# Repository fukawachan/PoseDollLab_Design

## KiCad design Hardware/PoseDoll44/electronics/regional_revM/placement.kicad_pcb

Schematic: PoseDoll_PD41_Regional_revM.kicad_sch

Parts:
C1: 10u X5R 25V / CL21A106KAYNNNE; C_0805_2012Metric
C2, C4: 22u X5R 16V / CL21A226MOYNNNE; C_0805_2012Metric
C3, C5, C7, C8, C21, C22, C23, C24, C25, C26, C27, C28, C29: 100n X7R; C_0603_1608Metric
C6: 1u X7R; C_0603_1608Metric
D1: PESD5V0S2BT,215; SOT-23
D2: TPD2E2U06DCKR; SOT-323_SC-70
J1: 5V from fused pelvis star; JST_PH_B2B-PH-SM4-TB_1x02-1MP_P2.00mm_Vertical
J2: CAN IN / GND-L-H; JST_GH_BM03B-GHS-TBT_1x03-1MP_P1.25mm_Vertical
J3: CAN OUT / GND-L-H; JST_GH_BM03B-GHS-TBT_1x03-1MP_P1.25mm_Vertical
J4: USB data only; external 5V required; USB_C_Data_Port
J11: P1 sensor / CS GPIO2; JST_SH_BM06B-SRSS-TB_1x06-1MP_P1.00mm_Vertical
J12: P2 sensor / CS GPIO4; JST_SH_BM06B-SRSS-TB_1x06-1MP_P1.00mm_Vertical
J13: P3 sensor / CS GPIO5; JST_SH_BM06B-SRSS-TB_1x06-1MP_P1.00mm_Vertical
J14: P4 sensor / CS GPIO6; JST_SH_BM06B-SRSS-TB_1x06-1MP_P1.00mm_Vertical
J15: P5 sensor / CS GPIO7; JST_SH_BM06B-SRSS-TB_1x06-1MP_P1.00mm_Vertical
J16: P6 sensor / CS GPIO8; JST_SH_BM06B-SRSS-TB_1x06-1MP_P1.00mm_Vertical
J17: P7 sensor / CS GPIO9; JST_SH_BM06B-SRSS-TB_1x06-1MP_P1.00mm_Vertical
J18: P8 sensor / CS GPIO10; JST_SH_BM06B-SRSS-TB_1x06-1MP_P1.00mm_Vertical
J19: P9 sensor / CS GPIO14; JST_SH_BM06B-SRSS-TB_1x06-1MP_P1.00mm_Vertical
JP1: CAN TERM: close endpoints only; PinHeader_1x02_P2.00mm_Vertical
L1: LSXND4040TKL2R2MDG / 2.2uH; L_Taiyo-Yuden_NR-40xx
Q1: MMBT3904; SOT-23
R1, R2, R4, R113, R117, R123, R127, R133, R137, R143, R147, R153, R157, R163, R167, R173, R177, R183, R187, R193, R197: 10k; R_0603_1608Metric
R3, R6, R7, R8, R116, R126, R136, R146, R156, R166, R176, R186, R196: 100k; R_0603_1608Metric
R5: 120R 1% 0.33W / CRCW0603120RFKEAHP; R_0603_1608Metric
R9, R10: 5.1k 1%; R_0603_1608Metric
R11, R12: 22R; R_0603_1608Metric
R110, R111, R112, R120, R121, R122, R130, R131, R132, R140, R141, R142, R150, R151, R152, R160, R161, R162, R170, R171, R172, R180, R181, R182, R190, R191, R192: 100R; R_0603_1608Metric
R114, R115, R124, R125, R134, R135, R144, R145, R154, R155, R164, R165, R174, R175, R184, R185, R194, R195: 47k; R_0603_1608Metric
SW1: RESET; SW_SPST_TL3305A
SW2: BOOT; SW_SPST_TL3305A
TP1: UART_TX; TestPoint_Pad_D1.0mm
TP2: UART_RX; TestPoint_Pad_D1.0mm
TP3: GND; TestPoint_Pad_D1.0mm
TP4: PG; TestPoint_Pad_D1.0mm
U1: ESP32-S3-WROOM-1-N8; ESP32-S3-WROOM-1
U2: TPS62162DSGR; Texas_DSG0008A_WSON-8-1EP_2x2mm_P0.5mm_EP0.9x1.6mm
U3: TCAN332DR; SOIC-8_3.9x4.9mm_P1.27mm
U4: TS3USB221ERSER; Texas_UQFN-10_1.5x2mm_P0.5mm
U11, U12, U13, U14, U15, U16, U17, U18, U19: SN74LVC125APWR; TSSOP-14_4.4x5mm_P0.65mm

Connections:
/+3V3: C2.1, C4.1, C5.1, C7.1, C8.1, C21.1, C22.1, C23.1, C24.1, C25.1, C26.1, C27.1, C28.1, C29.1, J11.2, J12.2, J13.2, J14.2, J15.2, J16.2, J17.2, J18.2, J19.2, L1.2, R1.1, R2.1, R3.1, R4.1, R8.1, R113.1, R117.1, R123.1, R127.1, R133.1, R137.1, R143.1, R147.1, R153.1, R157.1, R163.1, R167.1, R173.1, R177.1, R183.1, R187.1, R193.1, R197.1, U1.2 (3V3), U2.6 (VOS), U3.3 (VCC), U4.10 (VCC), U11.14 (VCC), U12.14 (VCC), U13.14 (VCC), U14.14 (VCC), U15.14 (VCC), U16.14 (VCC), U17.14 (VCC), U18.14 (VCC), U19.14 (VCC)
/+5V_IN: C1.1, C3.1, J1.1, U2.2 (VIN), U2.3 (EN)
/BOOT_N: R2.2, SW2.1, U1.27 (IO0)
/CAN_H: D1.2 (CAN2), J2.3, J3.3, R5.1, U3.7 (CANH)
/CAN_L: D1.1 (CAN1), J2.2, J3.2, JP1.2 (B), U3.6 (CANL)
/CAN_RX: U1.11 (IO18), U3.4 (RXD)
/CAN_TX: R4.2, U1.10 (IO17), U3.1 (TXD)
/CC1: J4.A5 (CC1), R9.1
/CC2: J4.B5 (CC2), R10.1
/CS1_MCU: R113.2, U1.38 (IO2), U11.1 (1OE_N), U11.4 (2OE_N), U11.10 (3OE_N), U11.12 (4A)
/CS2_MCU: R123.2, U1.4 (IO4), U12.1 (1OE_N), U12.4 (2OE_N), U12.10 (3OE_N), U12.12 (4A)
/CS3_MCU: R133.2, U1.5 (IO5), U13.1 (1OE_N), U13.4 (2OE_N), U13.10 (3OE_N), U13.12 (4A)
/CS4_MCU: R143.2, U1.6 (IO6), U14.1 (1OE_N), U14.4 (2OE_N), U14.10 (3OE_N), U14.12 (4A)
/CS5_MCU: R153.2, U1.7 (IO7), U15.1 (1OE_N), U15.4 (2OE_N), U15.10 (3OE_N), U15.12 (4A)
/CS6_MCU: R163.2, U1.12 (IO8), U16.1 (1OE_N), U16.4 (2OE_N), U16.10 (3OE_N), U16.12 (4A)
/CS7_MCU: R173.2, U1.17 (IO9), U17.1 (1OE_N), U17.4 (2OE_N), U17.10 (3OE_N), U17.12 (4A)
/CS8_MCU: R183.2, U1.18 (IO10), U18.1 (1OE_N), U18.4 (2OE_N), U18.10 (3OE_N), U18.12 (4A)
/CS9_MCU: R193.2, U1.22 (IO14), U19.1 (1OE_N), U19.4 (2OE_N), U19.10 (3OE_N), U19.12 (4A)
/EN: C6.1, R1.2, SW1.1, U1.3 (EN)
/GND: C1.2, C2.2, C3.2, C4.2, C5.2, C6.2, C7.2, C8.2, C21.2, C22.2, C23.2, C24.2, C25.2, C26.2, C27.2, C28.2, C29.2, D1.3 (GND), D2.3, J1.2, J2.1, J3.1, J4.A1 (GND), J4.A12 (GND), J4.B1 (GND), J4.B12 (GND), J4.SH (SHIELD), J11.1, J12.1, J13.1, J14.1, J15.1, J16.1, J17.1, J18.1, J19.1, Q1.2 (E), R7.2, R9.2, R10.2, R114.2, R115.2, R116.2, R124.2, R125.2, R126.2, R134.2, R135.2, R136.2, R144.2, R145.2, R146.2, R154.2, R155.2, R156.2, R164.2, R165.2, R166.2, R174.2, R175.2, R176.2, R184.2, R185.2, R186.2, R194.2, R195.2, R196.2, SW1.2, SW2.2, TP3.1, U1.1 (GND), U1.40 (GND), U1.41 (GND), U2.1 (PGND), U2.4 (AGND), U2.5 (FB), U2.9 (PAD), U3.2 (GND), U4.5 (GND), U4.9 (S), U11.7 (GND), U11.13 (4OE_N), U12.7 (GND), U12.13 (4OE_N), U13.7 (GND), U13.13 (4OE_N), U14.7 (GND), U14.13 (4OE_N), U15.7 (GND), U15.13 (4OE_N), U16.7 (GND), U16.13 (4OE_N), U17.7 (GND), U17.13 (4OE_N), U18.7 (GND), U18.13 (4OE_N), U19.7 (GND), U19.13 (4OE_N)
/P1_CS: J11.6, R112.2, R117.2
/P1_CS_DRV: R112.1, U11.11 (4Y)
/P1_MISO: J11.5, R116.1, U11.9 (3A)
/P1_MOSI: J11.4, R111.2, R115.1
/P1_MOSI_DRV: R111.1, U11.6 (2Y)
/P1_SCK: J11.3, R110.2, R114.1
/P1_SCK_DRV: R110.1, U11.3 (1Y)
/P2_CS: J12.6, R122.2, R127.2
/P2_CS_DRV: R122.1, U12.11 (4Y)
/P2_MISO: J12.5, R126.1, U12.9 (3A)
/P2_MOSI: J12.4, R121.2, R125.1
/P2_MOSI_DRV: R121.1, U12.6 (2Y)
/P2_SCK: J12.3, R120.2, R124.1
/P2_SCK_DRV: R120.1, U12.3 (1Y)
/P3_CS: J13.6, R132.2, R137.2
/P3_CS_DRV: R132.1, U13.11 (4Y)
/P3_MISO: J13.5, R136.1, U13.9 (3A)
/P3_MOSI: J13.4, R131.2, R135.1
/P3_MOSI_DRV: R131.1, U13.6 (2Y)
/P3_SCK: J13.3, R130.2, R134.1
/P3_SCK_DRV: R130.1, U13.3 (1Y)
/P4_CS: J14.6, R142.2, R147.2
/P4_CS_DRV: R142.1, U14.11 (4Y)
/P4_MISO: J14.5, R146.1, U14.9 (3A)
/P4_MOSI: J14.4, R141.2, R145.1
/P4_MOSI_DRV: R141.1, U14.6 (2Y)
/P4_SCK: J14.3, R140.2, R144.1
/P4_SCK_DRV: R140.1, U14.3 (1Y)
/P5_CS: J15.6, R152.2, R157.2
/P5_CS_DRV: R152.1, U15.11 (4Y)
/P5_MISO: J15.5, R156.1, U15.9 (3A)
/P5_MOSI: J15.4, R151.2, R155.1
/P5_MOSI_DRV: R151.1, U15.6 (2Y)
/P5_SCK: J15.3, R150.2, R154.1
/P5_SCK_DRV: R150.1, U15.3 (1Y)
/P6_CS: J16.6, R162.2, R167.2
/P6_CS_DRV: R162.1, U16.11 (4Y)
/P6_MISO: J16.5, R166.1, U16.9 (3A)
/P6_MOSI: J16.4, R161.2, R165.1
/P6_MOSI_DRV: R161.1, U16.6 (2Y)
/P6_SCK: J16.3, R160.2, R164.1
/P6_SCK_DRV: R160.1, U16.3 (1Y)
/P7_CS: J17.6, R172.2, R177.2
/P7_CS_DRV: R172.1, U17.11 (4Y)
/P7_MISO: J17.5, R176.1, U17.9 (3A)
/P7_MOSI: J17.4, R171.2, R175.1
/P7_MOSI_DRV: R171.1, U17.6 (2Y)
/P7_SCK: J17.3, R170.2, R174.1
/P7_SCK_DRV: R170.1, U17.3 (1Y)
/P8_CS: J18.6, R182.2, R187.2
/P8_CS_DRV: R182.1, U18.11 (4Y)
/P8_MISO: J18.5, R186.1, U18.9 (3A)
/P8_MOSI: J18.4, R181.2, R185.1
/P8_MOSI_DRV: R181.1, U18.6 (2Y)
/P8_SCK: J18.3, R180.2, R184.1
/P8_SCK_DRV: R180.1, U18.3 (1Y)
/P9_CS: J19.6, R192.2, R197.2
/P9_CS_DRV: R192.1, U19.11 (4Y)
/P9_MISO: J19.5, R196.1, U19.9 (3A)
/P9_MOSI: J19.4, R191.2, R195.1
/P9_MOSI_DRV: R191.1, U19.6 (2Y)
/P9_SCK: J19.3, R190.2, R194.1
/P9_SCK_DRV: R190.1, U19.3 (1Y)
/PG: R3.2, TP4.1, U2.8 (PG)
/SPI_MISO: U1.21 (IO13), U11.8 (3Y), U12.8 (3Y), U13.8 (3Y), U14.8 (3Y), U15.8 (3Y), U16.8 (3Y), U17.8 (3Y), U18.8 (3Y), U19.8 (3Y)
/SPI_MOSI: U1.19 (IO11), U11.5 (2A), U12.5 (2A), U13.5 (2A), U14.5 (2A), U15.5 (2A), U16.5 (2A), U17.5 (2A), U18.5 (2A), U19.5 (2A)
/SPI_SCK: U1.20 (IO12), U11.2 (1A), U12.2 (1A), U13.2 (1A), U14.2 (1A), U15.2 (1A), U16.2 (1A), U17.2 (1A), U18.2 (1A), U19.2 (1A)
/SW_BUCK: L1.1, U2.7 (SW)
/TERM_R: JP1.1 (A), R5.2
/UART_RX: TP2.1, U1.36 (RXD0)
/UART_TX: TP1.1, U1.37 (TXD0)
/USB_DM_HOST: D2.2, J4.A7 (D-), J4.B7 (D-), U4.7 (D-)
/USB_DM_IC: R12.2, U1.13 (USB_D-)
/USB_DM_SW: R12.1, U4.2 (1D-)
/USB_DP_HOST: D2.1, J4.A6 (D+), J4.B6 (D+), U4.8 (D+)
/USB_DP_IC: R11.2, U1.14 (USB_D+)
/USB_DP_SW: R11.1, U4.1 (1D+)
/USB_OE_N: Q1.3 (C), R8.2, U4.6 (OE_N)
/VBUS_BASE: Q1.1 (B), R6.2, R7.1
/VBUS_USB: J4.A4 (VBUS), J4.A9 (VBUS), J4.B4 (VBUS), J4.B9 (VBUS), R6.1

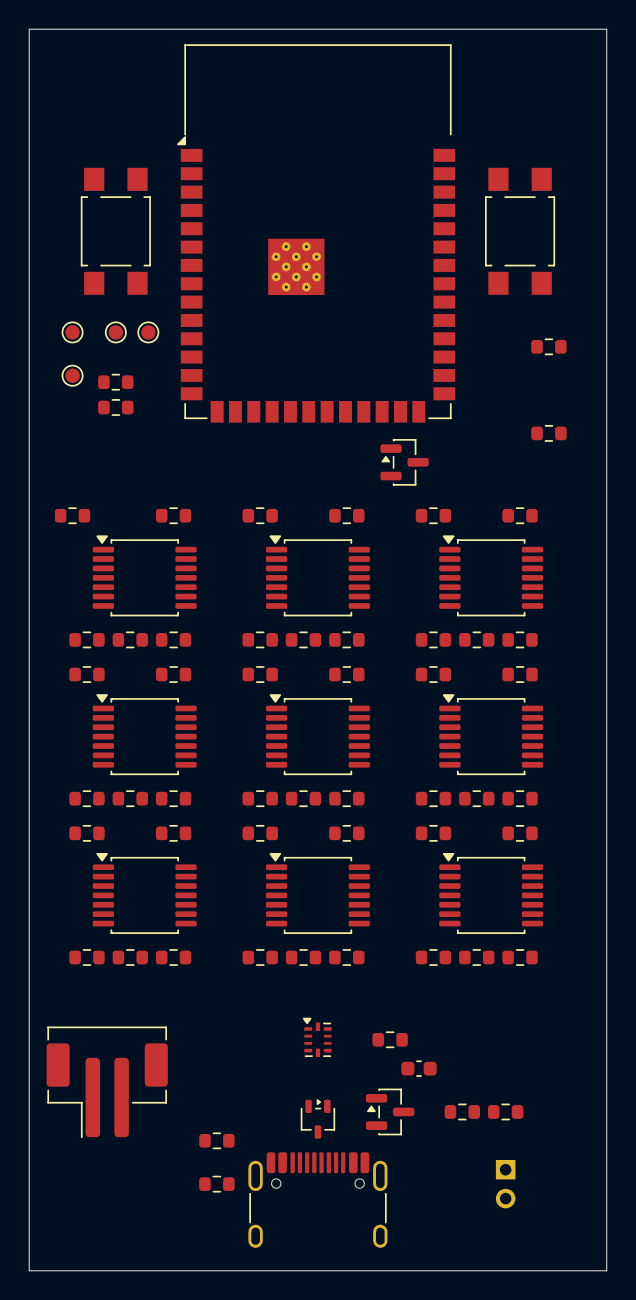
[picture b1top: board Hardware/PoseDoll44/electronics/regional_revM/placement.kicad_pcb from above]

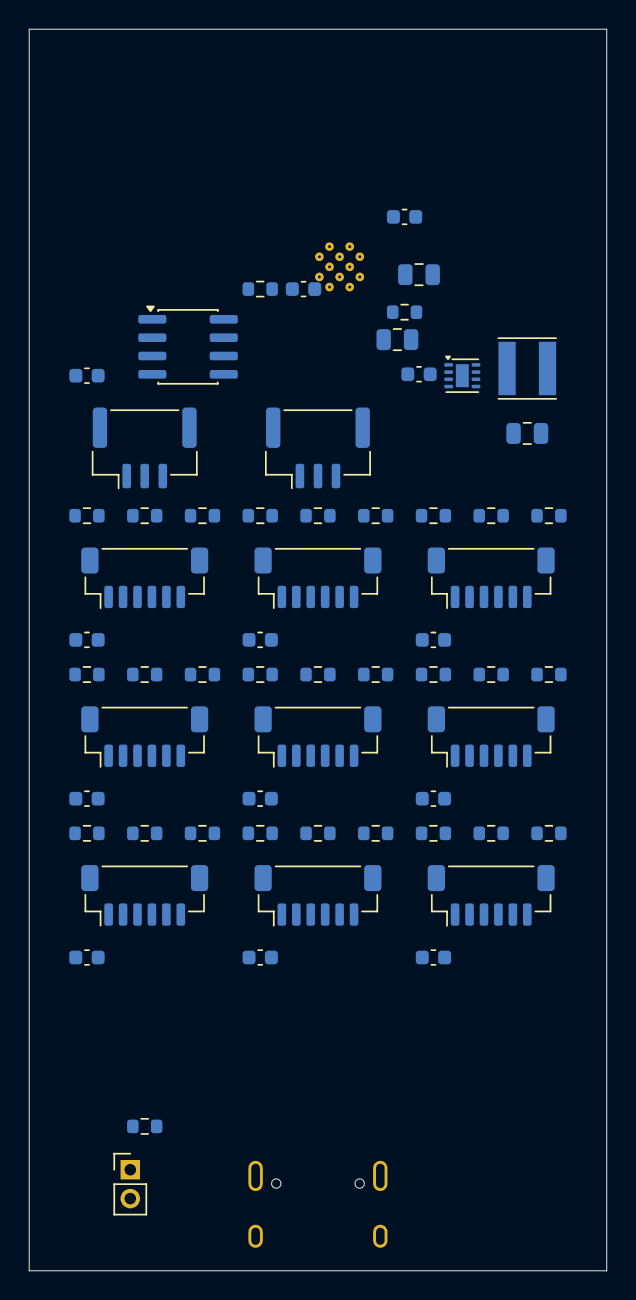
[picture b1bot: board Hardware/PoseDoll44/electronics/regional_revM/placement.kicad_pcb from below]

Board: 4 copper layers, 40.0 x 86.0 mm, 138 parts (61 on the bottom side), 100 nets, no tracks yet.

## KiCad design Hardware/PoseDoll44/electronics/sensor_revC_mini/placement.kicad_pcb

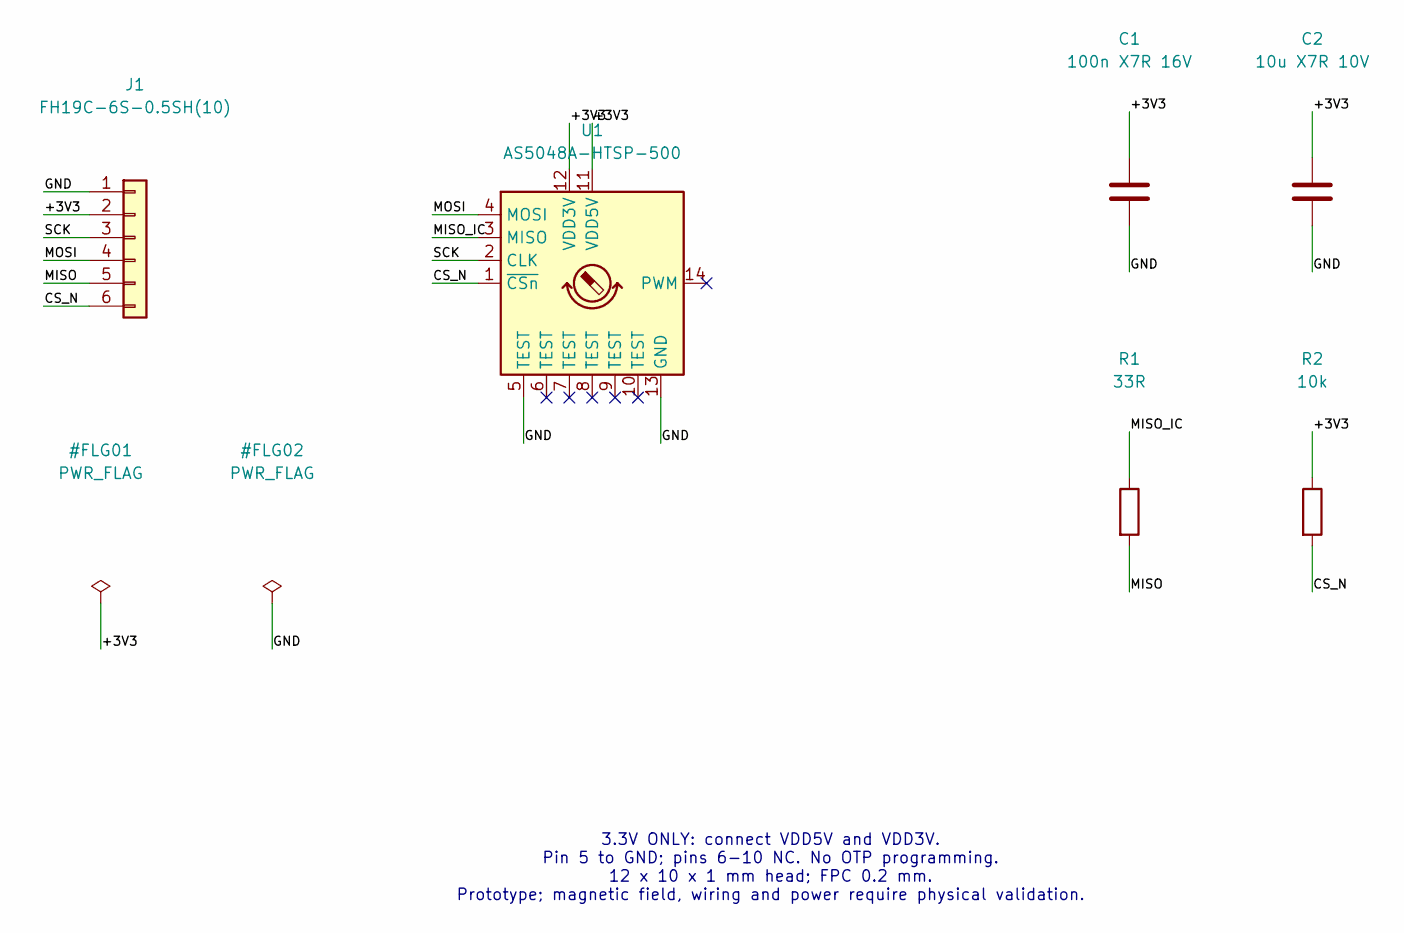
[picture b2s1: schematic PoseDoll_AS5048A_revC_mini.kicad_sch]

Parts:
C1: 100n X7R 16V; C_0603_1608Metric
C2: 10u X7R 10V; C_0805_2012Metric
J1: FH19C-6S-0.5SH(10); Hirose_FH19C_6S_0.5SH
R1: 33R; R_0603_1608Metric
R2: 10k; R_0603_1608Metric
U1: AS5048A-HTSP-500; TSSOP-14_4.4x5mm_P0.65mm

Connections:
/+3V3: C1.1, C2.1, J1.2, R2.1, U1.11 (VDD5V), U1.12 (VDD3V)
/CS_N: J1.6, R2.2, U1.1 (~CSn)
/GND: C1.2, C2.2, J1.1, U1.5 (TEST), U1.13 (GND)
/MISO: J1.5, R1.2
/MISO_IC: R1.1, U1.3 (MISO)
/MOSI: J1.4, U1.4 (MOSI)
/SCK: J1.3, U1.2 (CLK)

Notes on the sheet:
3.3V ONLY: connect VDD5V and VDD3V. Pin 5 to GND; pins 6-10 NC. No OTP programming. 12 x 10 x 1 mm head; FPC 0.2 mm. Prototype; magnetic field, wiring and power require physical validation.

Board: 2 copper layers, 6 parts (1 on the bottom side), 7 nets, no tracks yet.
